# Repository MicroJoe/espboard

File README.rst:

ESP8266 board
#############

A small board for ESP8266 ESP-1 circuits. Micro USB adapters can be found here_.

.. _here: https://www.aliexpress.com/item/10pcs-MICRO-USB-to-DIP-Adapter-5pin-female-connector-B-type-pcb-converter-pinboard-2-54/32667278609.html

Schema
======

.. image:: schema.png

PCB
===

.. image:: pcb.png

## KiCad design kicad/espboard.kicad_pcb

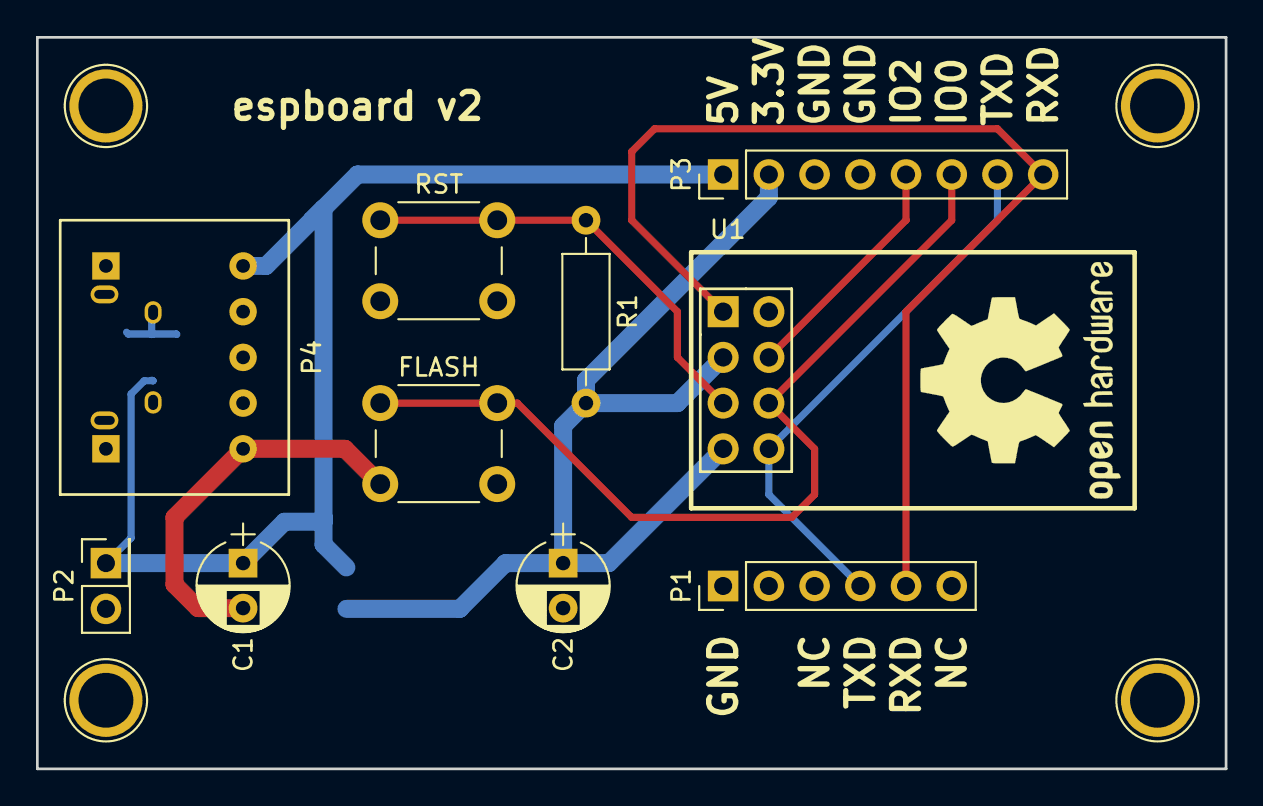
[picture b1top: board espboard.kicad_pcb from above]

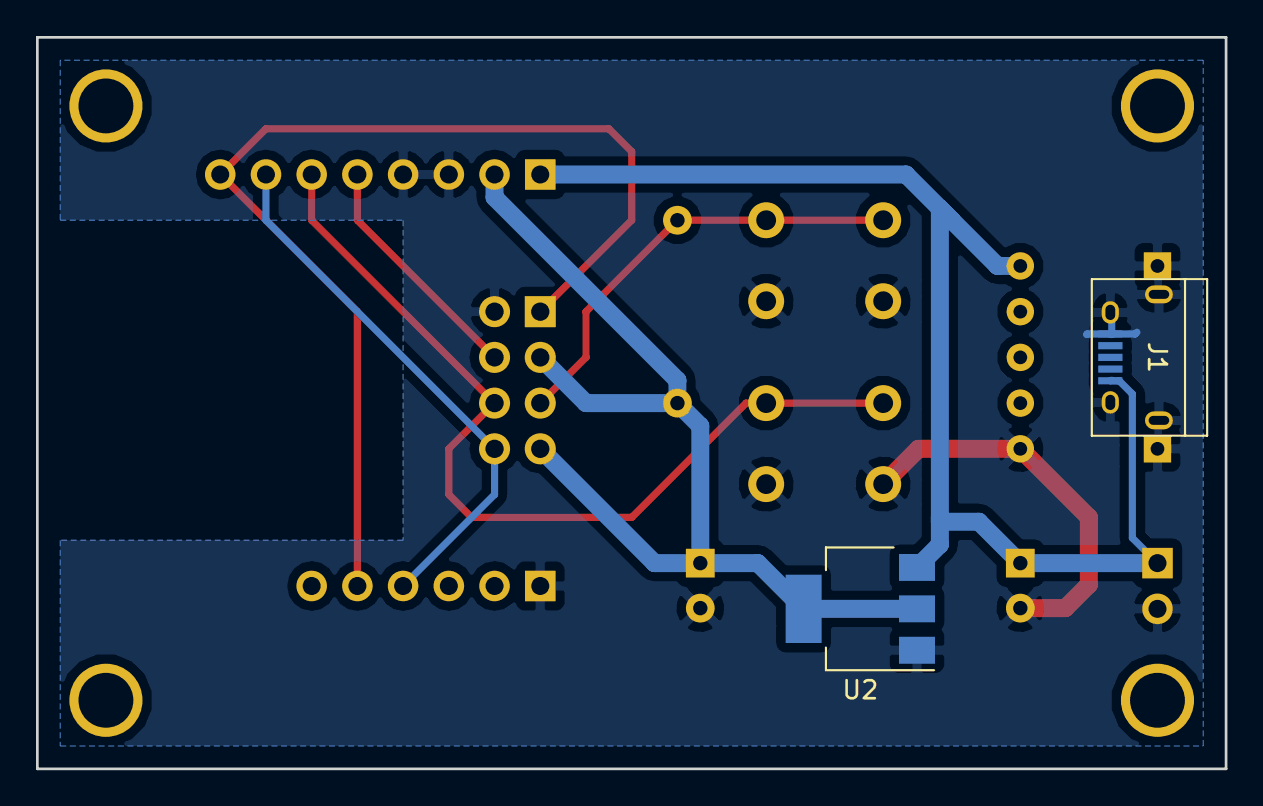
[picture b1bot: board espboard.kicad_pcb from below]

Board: 2 copper layers, 66.0 x 40.6 mm, 12 parts (2 on the bottom side), 8 nets.

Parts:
C1, C2: 10u; CP_Radial_D5.0mm_P2.50mm
FLASH: SW_FLASH; SW_PUSH_6mm
J1: USB_OTG; USB_Micro-B
P1: ftdi; Pin_Header_Straight_1x06_Pitch2.54mm
P2: CONN_PWR; Socket_Strip_Straight_2x01_Pitch2.54mm
P3: CONN_IO; Socket_Strip_Straight_1x08_Pitch2.54mm
P4: usb_connector; usb_adapter
R1: 10k; R_Axial_DIN0207_L6.3mm_D2.5mm_P10.16mm_Horizontal
RST: SW_RST; SW_PUSH_6mm
U1: ESP-01v090; ESP-01
U2: LM1117-3.3; SOT-223

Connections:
ESP_GPIO0: FLASH.1, P3.6, U1.6
ESP_GPIO2: P3.5, U1.4
GND: C1.2, C2.2, FLASH.2, J1.5, J1.6, P1.1, P2.2, P3.3, P3.4, P4.1, P4.6, RST.2, U1.2, U2.1
unnamed: R1.1, RST.1, U1.5
PWR_3V3: C2.1, P3.2, R1.2, U1.3, U1.7, U2.2, U2.4
PWR_5V: C1.1, J1.1, P2.1, P3.1, P4.5, U2.3
UART_RXD: P1.5, P3.8, U1.1
UART_TXD: P1.4, P3.7, U1.8

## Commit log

2017-02-15 All new KiCAD project
2017-02-15 Added README
2017-02-15 Added pictures
2017-02-15 Fix plan de masse et ajout texte
2017-02-15 Finalize PCB sheet
2017-02-15 Updated PCB preview
2017-02-17 Bigger vias
2017-02-18 Fix NC for 3V3
2017-02-18 Removed out-of-date screenshots
2017-09-13 Commit v2
2017-09-15 Added pictures, bom...
2017-09-23 Add link to USB adapters

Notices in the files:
kicad/espboard.kicad_pcb:
Creative Commons BY-SA
